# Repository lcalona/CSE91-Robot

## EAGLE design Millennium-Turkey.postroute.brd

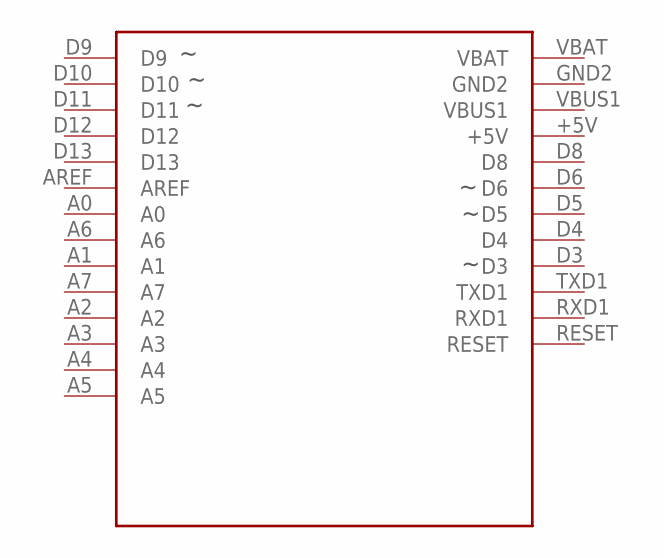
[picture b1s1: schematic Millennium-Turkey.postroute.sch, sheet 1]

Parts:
U3: ADAFRUIT-PRO-TRINKET-5V-NOFTDI

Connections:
+5V_0_BRAIN: U3.+5V; also elsewhere on the board
A0_0_BRAIN: U3.A0; also elsewhere on the board
A1_0_BRAIN: U3.A1
A2_0_BRAIN: U3.A2
A3_0_BRAIN: U3.A3
A4_0_BRAIN: U3.A4; also elsewhere on the board
A5_0_BRAIN: U3.A5; also elsewhere on the board
A6_0_BRAIN: U3.A6
A7_0_BRAIN: U3.A7
AREF_0_BRAIN: U3.AREF
D3_0_BRAIN: U3.D3; also elsewhere on the board
D4_0_BRAIN: U3.D4; also elsewhere on the board
D5_0_BRAIN: U3.D5; also elsewhere on the board
D6_0_BRAIN: U3.D6; also elsewhere on the board
D8_0_BRAIN: U3.D8; also elsewhere on the board
D9_0_BRAIN: U3.D9; also elsewhere on the board
D10_0_BRAIN: U3.D10; also elsewhere on the board
D11_0_BRAIN: U3.D11; also elsewhere on the board
D12_0_BRAIN: U3.D12; also elsewhere on the board
D13_0_BRAIN: U3.D13
GND_0_BRAIN: U3.GND2; also elsewhere on the board
POS_1_BATTERY: U3.VBAT; also elsewhere on the board
RESET_0_BRAIN: U3.RESET
RXD1_0_BRAIN: U3.RXD1
TXD1_0_BRAIN: U3.TXD1
VBUS1_0_BRAIN: U3.VBUS1

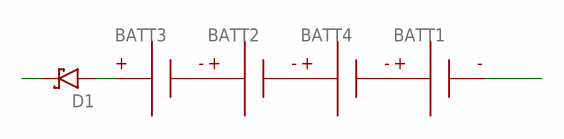
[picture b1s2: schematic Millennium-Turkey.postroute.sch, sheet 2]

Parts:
BATT1, BATT2, BATT3, BATT4: BATTERY-AA-CLIP; BATTERY-AA-BK-92
D1: RESOLVED-DIODE-SCHOTTKY_TH-DO-41-AND-DO-204AL; DIOAD1125W78L520D270_HS; MPN 1N5817

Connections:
GND_0_BRAIN: BATT1.N1 (N), BATT1.N2 (N); also elsewhere on the board
unnamed: BATT2.P1, BATT2.P2, BATT3.N1 (N), BATT3.N2 (N)
unnamed: BATT2.N1 (N), BATT2.N2 (N), BATT4.P1, BATT4.P2
unnamed: BATT1.P1, BATT1.P2, BATT4.N1 (N), BATT4.N2 (N)
unnamed: BATT3.P1, BATT3.P2, D1.A
POS_1_BATTERY: D1.C; also elsewhere on the board

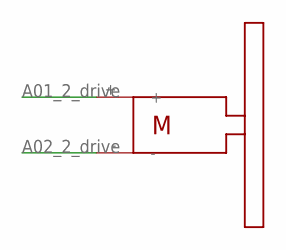
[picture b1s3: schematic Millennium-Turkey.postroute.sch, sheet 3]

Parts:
U2: SOLARBOTICS_GM2; SOLARBOTICS_G2

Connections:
A01_2_DRIVE: U2.+; also elsewhere on the board
A02_2_DRIVE: U2.-; also elsewhere on the board

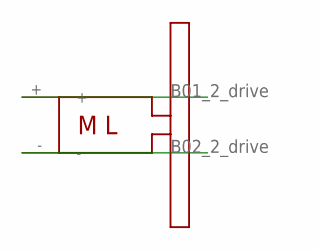
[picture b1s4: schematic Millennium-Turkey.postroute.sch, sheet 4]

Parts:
U4: SOLARBOTICS_GM2_LEFT; SOLARBOTICS_G2_LEFT

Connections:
B01_2_DRIVE: U4.+; also elsewhere on the board
B02_2_DRIVE: U4.-; also elsewhere on the board

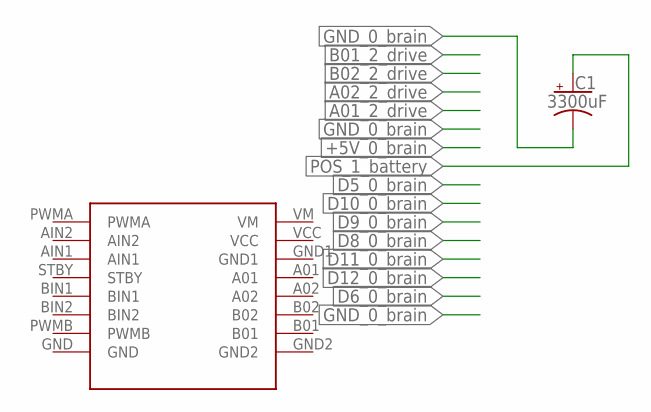
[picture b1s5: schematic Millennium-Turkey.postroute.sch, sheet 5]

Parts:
C1: 3300uF; CAPPRD750W80D1600H2200P; MPN ECA-1EM332
U1: SPARKFUN_DUAL_MOTOR_DRIVER-BOB; SPARKFUN_DUAL_MOTOR_DRIVER

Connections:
+5V_0_BRAIN: U1.VCC; also elsewhere on the board
A01_2_DRIVE: U1.A01; also elsewhere on the board
A02_2_DRIVE: U1.A02; also elsewhere on the board
B01_2_DRIVE: U1.B01; also elsewhere on the board
B02_2_DRIVE: U1.B02; also elsewhere on the board
D5_0_BRAIN: U1.PWMA; also elsewhere on the board
D6_0_BRAIN: U1.PWMB; also elsewhere on the board
D8_0_BRAIN: U1.STBY; also elsewhere on the board
D9_0_BRAIN: U1.AIN1; also elsewhere on the board
D10_0_BRAIN: U1.AIN2; also elsewhere on the board
D11_0_BRAIN: U1.BIN1; also elsewhere on the board
D12_0_BRAIN: U1.BIN2; also elsewhere on the board
GND_0_BRAIN: C1.2 (-), U1.GND, U1.GND1, U1.GND2; also elsewhere on the board
POS_1_BATTERY: C1.1 (+), U1.VM; also elsewhere on the board

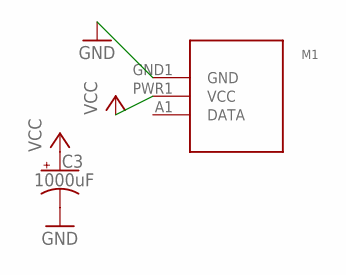
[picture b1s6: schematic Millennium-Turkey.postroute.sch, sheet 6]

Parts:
C3: 1000uF; CAPPRD500W80D1000H2200P; MPN ECA-1EM102
M1: SERVO-MICRO_SIDE_GLUE; SERVO_MICRO_SIDE_GLUE

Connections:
D3_0_BRAIN: M1.A1 (DATA); also elsewhere on the board
GND_0_BRAIN: C3.2 (-), M1.GND1 (GND); also elsewhere on the board
POS_1_BATTERY: C3.1 (+), M1.PWR1 (VCC); also elsewhere on the board

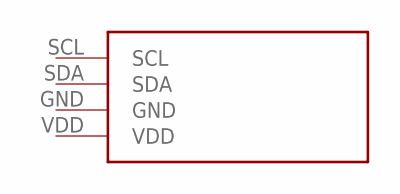
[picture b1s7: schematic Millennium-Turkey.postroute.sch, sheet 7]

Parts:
U6: ADAFRUIT-1.2IN-8X8-LED-BACKPACK-WHITE; ADAFRUIT-1.2IN-8X8-LED-BACKPACK

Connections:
+5V_0_BRAIN: U6.VDD; also elsewhere on the board
A4_0_BRAIN: U6.SDA; also elsewhere on the board
A5_0_BRAIN: U6.SCL; also elsewhere on the board
GND_0_BRAIN: U6.GND; also elsewhere on the board

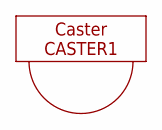
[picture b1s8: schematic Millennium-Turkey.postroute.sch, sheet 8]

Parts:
CASTER1: CASTERADAFRUIT-3/4IN; ADAFRUIT-3/4IN-CASTER

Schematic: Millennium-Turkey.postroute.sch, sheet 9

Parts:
C2: 100uF; CAPPRD250W80D630H1220P; MPN ECA-1EM101
U5: ANALOG_DISTANCE_SENSOR-GLUE; ANALOG_DISTANCE_SENSOR_GLUE_MOUNT

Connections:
+5V_0_BRAIN: C2.1 (+), U5.VCC; also elsewhere on the board
A0_0_BRAIN: U5.VO (A); also elsewhere on the board
GND_0_BRAIN: C2.2 (-), U5.GND; also elsewhere on the board

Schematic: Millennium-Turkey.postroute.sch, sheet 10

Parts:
B1: BUZZER-ADAFRUIT-160; BUZZER-12MM-ADAFRUIT-160

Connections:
D4_0_BRAIN: B1.+ (1); also elsewhere on the board
GND_0_BRAIN: B1.- (2); also elsewhere on the board

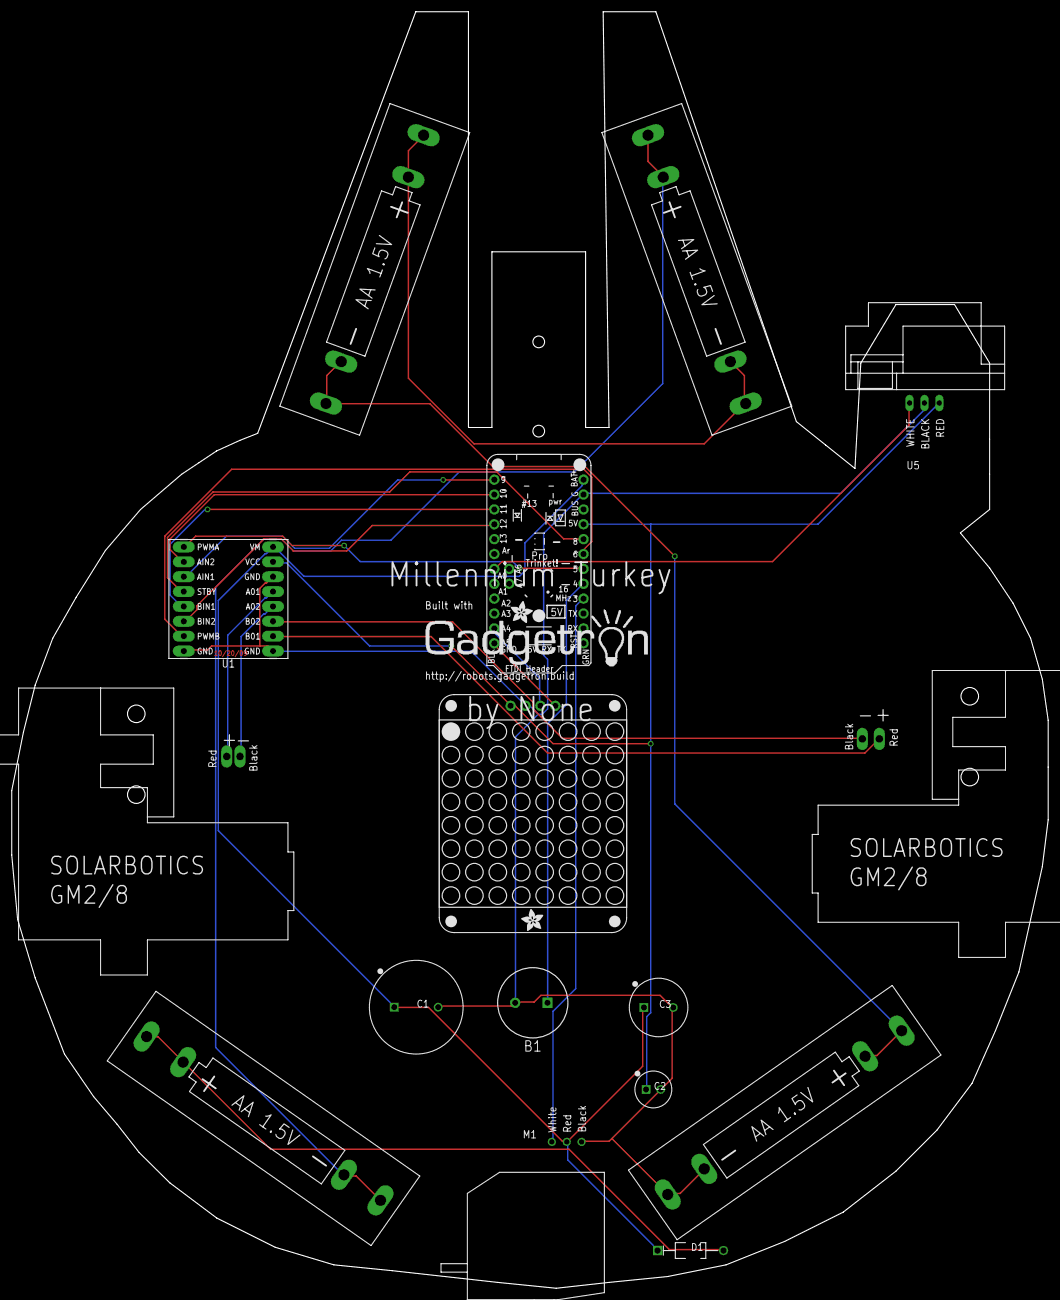
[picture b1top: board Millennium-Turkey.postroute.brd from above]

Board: 2 copper layers, 177.0 x 218.0 mm, 18 parts (0 on the bottom side), 23 nets.

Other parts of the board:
LOGO: BUILT_WITH_GADGETRON

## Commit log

2017-03-01 :tada: Added .gitattributes & .gitignore files
2017-03-01 Files for robot
